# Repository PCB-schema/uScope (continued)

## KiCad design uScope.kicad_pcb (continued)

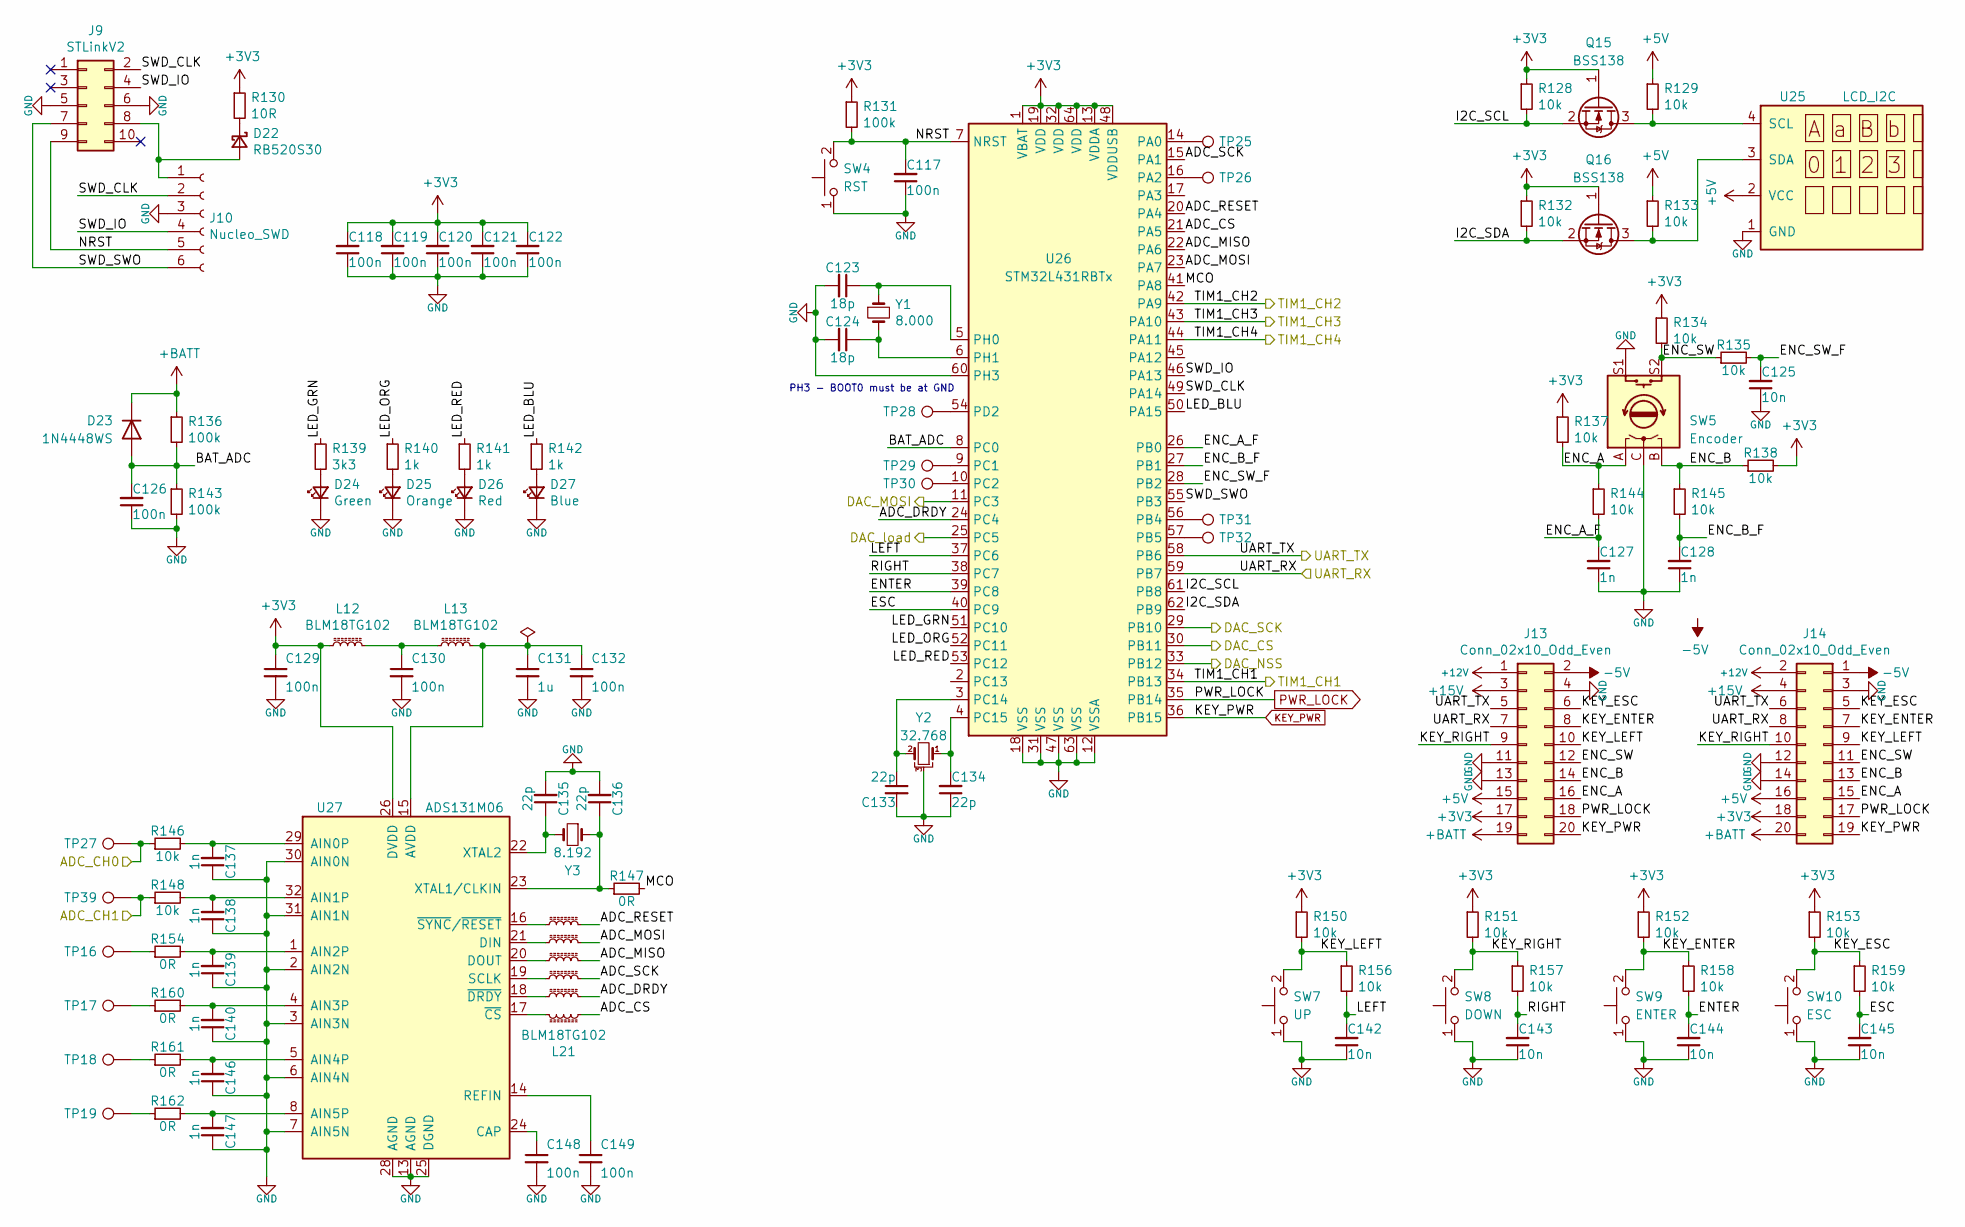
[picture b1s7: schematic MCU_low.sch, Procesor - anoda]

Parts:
C117, C118, C119, C120, C121, C122, C126, C129, C130, C132, C148, C149: 100n; C_0603_1608Metric
C123, C124: 18p; C_0603_1608Metric
C125, C142, C143, C144, C145: 10n; C_0603_1608Metric
C127, C128, C137, C138, C139, C140, C146, C147: 1n; C_0603_1608Metric
C131: 1u; C_0603_1608Metric
C133, C134, C135, C136: 22p; C_0603_1608Metric
D22: RB520S30; D_SOD-323-523_HandSoldering
D23: 1N4448WS; D_SOD-323-523_HandSoldering
D24: Green; D_0805_2012Metric_Pad1.15x1.40mm_HandSolder
D25: Orange; D_0805_2012Metric_Pad1.15x1.40mm_HandSolder
D26: Red; D_0805_2012Metric_Pad1.15x1.40mm_HandSolder
D27: Blue; D_0805_2012Metric_Pad1.15x1.40mm_HandSolder
J9: STLinkV2; ST-LinkV2_FakeStm8Stm32_vertical
J10: Nucleo_SWD; PinSocket_1x06_P2.54mm_Vertical
J13, J14: Conn_02x10_Odd_Even; PinSocket_2x10_P2.54mm_Vertical
L12, L13, L16, L17, L18, L19, L20, L21: BLM18TG102; L_0603_1608Metric
Q15, Q16: BSS138; SOT-23
R128, R129, R132, R133, R134, R135, R137, R138, R144, R145, R146, R148, R150, R151, R152, R153, R156, R157, R158, R159: 10k; R_0603_1608Metric
R130: 10R; R_0603_1608Metric
R131, R136, R143: 100k; R_0603_1608Metric
R139: 3k3; R_0603_1608Metric
R140, R141, R142: 1k; R_0603_1608Metric
R147, R154, R160, R161, R162: 0R; R_0603_1608Metric
SW4: RST; SW_Push_1P1T_NO_6x6mm_H9.5mm
SW5: Encoder; Encoder_12.4x13.4_pitch2.5mm_wSw
SW7: UP; SW_Push_1P1T_NO_6x6mm_H9.5mm
SW8: DOWN; SW_Push_1P1T_NO_6x6mm_H9.5mm
SW9: ENTER; SW_Push_1P1T_NO_6x6mm_H9.5mm
SW10: ESC; SW_Push_1P1T_NO_6x6mm_H9.5mm
TP16, TP17, TP18, TP19, TP25, TP26, TP27, TP28, TP29, TP30, TP31, TP32, TP39: TestPoint; TestPoint_THTPad_D1.5mm_Drill0.7mm
U25: LCD_I2C; PinHeader_1x04_P2.54mm_Vertical
U26: STM32L431RBTx; LQFP-64_10x10mm_P0.5mm
U27: ADS131M06; TQFP-32_5x5mm_P0.5mm_edges
Y1: 8.000; Crystal_HC49-4H_Vertical
Y2: 32.768; Crystal_C38-LF_D3.0mm_L8.0mm_Horizontal_1EP_style1
Y3: 8.192; Crystal_HC49-4H_Vertical

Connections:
+3V3: C118.2, C119.2, C120.2, C121.2, C122.2, C129.1, J13.17, J14.18, L12.1, Q15.1 (G), Q16.1 (G), R128.1, R130.1, R131.1, R132.1, R134.1, R137.1, R138.2, R150.1, R151.1, R152.1, R153.1, U26.1 (VBAT), U26.13 (VDDA), U26.19 (VDD), U26.32 (VDD), U26.48 (VDDUSB), U26.64 (VDD), U27.26 (DVDD); also elsewhere on the board
+5V: J13.15, J14.16, R129.1, R133.1, U25.2 (VCC); also elsewhere on the board
+12V: J13.1, J14.2; also elsewhere on the board
+15V: J13.3, J14.4; also elsewhere on the board
-5V: J13.2, J14.1; also elsewhere on the board
/ADC_IK: R146.1, TP27.1; also elsewhere on the board
/ADC_UK: R148.1, TP39.1; also elsewhere on the board
/LV_UART_RX: J13.7, J14.8, U26.59 (PB7); also elsewhere on the board
/LV_UART_TX: J13.5, J14.6, U26.58 (PB6); also elsewhere on the board
/MCU_low/ADC_CS: L21.1, U26.21 (PA5)
/MCU_low/ADC_DRDY: L20.2, U26.24 (PC4)
/MCU_low/ADC_MISO: L18.2, U26.22 (PA6)
/MCU_low/ADC_MOSI: L17.2, U26.23 (PA7)
/MCU_low/ADC_RESET: L16.2, U26.20 (PA4)
/MCU_low/ADC_SCK: L19.2, U26.15 (PA1)
/MCU_low/BAT_ADC: C126.2, D23.2 (A), R136.2, R143.1, U26.8 (PC0)
/MCU_low/DAC_CS: U26.30 (PB11); also elsewhere on the board
/MCU_low/DAC_MOSI: U26.11 (PC3); also elsewhere on the board
/MCU_low/DAC_NSS: U26.33 (PB12); also elsewhere on the board
/MCU_low/DAC_SCK: U26.29 (PB10); also elsewhere on the board
/MCU_low/DAC_load: U26.25 (PC5); also elsewhere on the board
/MCU_low/ENC_A: J13.16, J14.15, R137.2, R144.1, SW5.A
/MCU_low/ENC_A_F: C127.2, R144.2, U26.26 (PB0)
/MCU_low/ENC_B: J13.14, J14.13, R138.1, R145.1, SW5.B
/MCU_low/ENC_B_F: C128.2, R145.2, U26.27 (PB1)
/MCU_low/ENC_SW: J13.12, J14.11, R134.2, R135.1, SW5.S2
/MCU_low/ENC_SW_F: C125.2, R135.2, U26.28 (PB2)
/MCU_low/ENTER: C144.2, R158.2, U26.39 (PC8)
/MCU_low/ESC: C145.2, R159.2, U26.40 (PC9)
/MCU_low/I2C_SCL: Q15.2 (S), R128.2, U26.61 (PB8)
/MCU_low/I2C_SDA: Q16.2 (S), R132.2, U26.62 (PB9)
/MCU_low/KEY_ENTER: J13.8, J14.7, R152.2, R158.1, SW9.2
/MCU_low/KEY_ESC: J13.6, J14.5, R153.2, R159.1, SW10.2
/MCU_low/KEY_LEFT: J13.10, J14.9, R150.2, R156.1, SW7.2
/MCU_low/KEY_RIGHT: J13.9, J14.10, R151.2, R157.1, SW8.2
/MCU_low/LED_BLU: R142.1, U26.50 (PA15)
/MCU_low/LED_GRN: R139.1, U26.51 (PC10)
/MCU_low/LED_ORG: R140.1, U26.52 (PC11)
/MCU_low/LED_RED: R141.1, U26.53 (PC12)
/MCU_low/LEFT: C142.2, R156.2, U26.37 (PC6)
/MCU_low/MCO: R147.2, U26.41 (PA8)
/MCU_low/NRST: C117.2, J9.9, J10.5, R131.2, SW4.2, U26.7 (NRST)
/MCU_low/RIGHT: C143.2, R157.2, U26.38 (PC7)
/MCU_low/SWD_CLK: J9.2, J10.2, U26.49 (PA14)
/MCU_low/SWD_IO: J9.4, J10.4, U26.46 (PA13)
/MCU_low/SWD_SWO: J9.7, J10.6, U26.55 (PB3)
/MCU_low/TIM1_CH1: U26.34 (PB13); also elsewhere on the board
/MCU_low/TIM1_CH2: U26.42 (PA9); also elsewhere on the board
/MCU_low/TIM1_CH3: U26.43 (PA10); also elsewhere on the board
/MCU_low/TIM1_CH4: U26.44 (PA11); also elsewhere on the board
KEY_PWR: J13.20, J14.19, U26.36 (PB15); also elsewhere on the board
unnamed: C123.1, U26.5 (PH0), Y1.1
unnamed: C124.1, U26.6 (PH1), Y1.2
unnamed: C130.1, L12.2, L13.1
unnamed: C131.1, C132.1, L13.2, U27.15 (AVDD)
unnamed: C133.1, U26.3 (PC14), Y2.2
unnamed: C134.2, U26.4 (PC15), Y2.1
unnamed: C135.1, U27.22 (XTAL2), Y3.2
unnamed: C136.1, R147.1, U27.23 (XTAL1/CLKIN), Y3.1
unnamed: C137.2, R146.2, U27.29 (AIN0P)
unnamed: C138.2, R148.2, U27.32 (AIN1P)
unnamed: C139.2, R154.2, U27.1 (AIN2P)
unnamed: C140.2, R160.2, U27.4 (AIN3P)
unnamed: C146.2, R161.2, U27.5 (AIN4P)
unnamed: C147.2, R162.2, U27.8 (AIN5P)
unnamed: C148.1, U27.24 (CAP)
unnamed: C149.1, U27.14 (REFIN)
unnamed: D22.1 (K), R130.2
unnamed: D22.2 (A), J9.8, J10.1
unnamed: D24.2 (A), R139.2
unnamed: D25.2 (A), R140.2
unnamed: D26.2 (A), R141.2
unnamed: D27.2 (A), R142.2
unnamed: L16.1, U27.16 (~SYNC~/~RESET)
unnamed: L17.1, U27.21 (DIN)
unnamed: L18.1, U27.20 (DOUT)
unnamed: L19.1, U27.19 (SCLK)
unnamed: L20.1, U27.18 (~DRDY)
unnamed: L21.2, U27.17 (~CS)
unnamed: Q15.3 (D), R129.2, U25.4 (SCL)
unnamed: Q16.3 (D), R133.2, U25.3 (SDA)
unnamed: R154.1, TP16.1
unnamed: R160.1, TP17.1
unnamed: R161.1, TP18.1
unnamed: R162.1, TP19.1
unnamed: TP25.1, U26.14 (PA0)
unnamed: TP26.1, U26.16 (PA2)
unnamed: TP28.1, U26.54 (PD2)
unnamed: TP29.1, U26.9 (PC1)
unnamed: TP30.1, U26.10 (PC2)
unnamed: TP31.1, U26.56 (PB4)
unnamed: TP32.1, U26.57 (PB5)
PWR_LOCK: J13.18, J14.17, U26.35 (PB14); also elsewhere on the board

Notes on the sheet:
PH3 - BOOT0 must be at GND

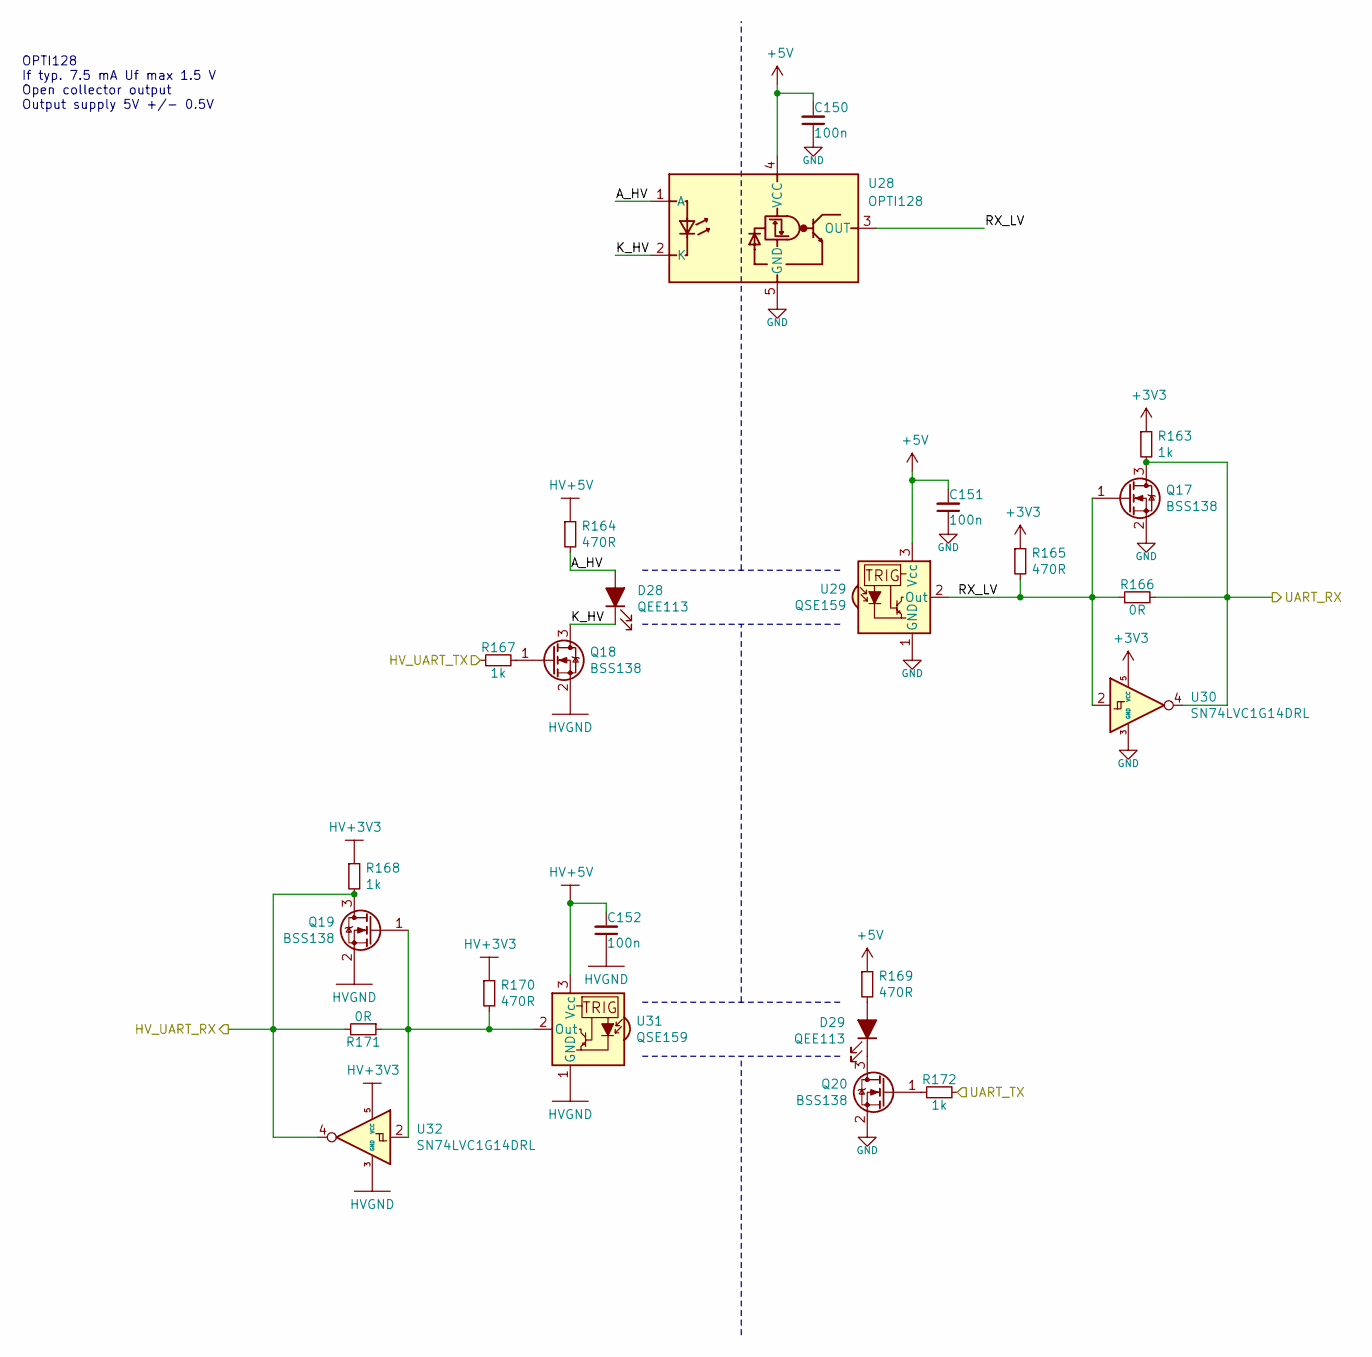
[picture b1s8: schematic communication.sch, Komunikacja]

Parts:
C150, C151, C152: 100n; C_0603_1608Metric
D28, D29: QEE113; ONsemi_QEE113
Q17, Q18, Q19, Q20: BSS138; SOT-23
R163, R167, R168, R172: 1k; R_0603_1608Metric
R164, R165, R169, R170: 470R; R_0603_1608Metric
R166, R171: 0R; R_0603_1608Metric
U28: OPTI128; OPTI12x
U29, U31: QSE159; ONSemi_QSE15x
U30, U32: SN74LVC1G14DRL; SOT-553

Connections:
+3V3: R163.1, R165.1, U30.5 (VCC); also elsewhere on the board
+5V: C150.2, C151.2, R169.1, U28.4 (VCC), U29.3 (Vcc); also elsewhere on the board
/HV_UART_RX: Q19.3 (D), R168.2, R171.2, U32.4; also elsewhere on the board
/HV_UART_TX: R167.1; also elsewhere on the board
/LV_UART_RX: Q17.3 (D), R163.2, R166.2, U30.4; also elsewhere on the board
/LV_UART_TX: R172.2; also elsewhere on the board
/communication/A_HV: D28.2 (A), R164.2, U28.1 (A)
/communication/K_HV: D28.1 (K), Q18.3 (D), U28.2 (K)
/communication/RX_LV: Q17.1 (G), R165.2, R166.1, U28.3 (OUT), U29.2 (Out), U30.2
HV+3V3: R168.1, R170.1, U32.5 (VCC); also elsewhere on the board
HV+5V: C152.2, R164.1, U31.3 (Vcc); also elsewhere on the board
unnamed: D29.1 (K), Q20.3 (D)
unnamed: D29.2 (A), R169.2
unnamed: Q18.1 (G), R167.2
unnamed: Q19.1 (G), R170.2, R171.1, U31.2 (Out), U32.2
unnamed: Q20.1 (G), R172.1

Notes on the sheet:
OPTI128 If typ. 7.5 mA Uf max 1.5 V Open collector output Output supply 5V +/- 0.5V

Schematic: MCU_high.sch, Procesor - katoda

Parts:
C153, C154, C156, C160, C161, C162, C163, C164, C169, C171, C172: 100n; C_0603_1608Metric
C155: 1u; C_0603_1608Metric
C157, C158, C175, C176: 22p; C_0603_1608Metric
C159, C165, C166, C167, C168, C170: 1n; C_0603_1608Metric
C173, C174: 18p; C_0603_1608Metric
D30: RB520S30; D_SOD-323-523_HandSoldering
D31: Green; D_0805_2012Metric_Pad1.15x1.40mm_HandSolder
D32: Orange; D_0805_2012Metric_Pad1.15x1.40mm_HandSolder
D33: Red; D_0805_2012Metric_Pad1.15x1.40mm_HandSolder
D34: Blue; D_0805_2012Metric_Pad1.15x1.40mm_HandSolder
J11: STLinkV2; ST-LinkV2_FakeStm8Stm32_vertical
J12: Nucleo_SWD; PinSocket_1x06_P2.54mm_Vertical
J15, J16: Conn_02x03_Odd_Even; PinSocket_2x03_P2.54mm_Vertical
L14, L15, L22, L23, L24, L25, L26, L27: BLM18TG102; L_0603_1608Metric
R173: 10R; R_0603_1608Metric
R174, R176: 10k; R_0603_1608Metric
R175, R177, R178, R181, R182: 0R; R_0603_1608Metric
R180: 100k; R_0603_1608Metric
R183: 3k3; R_0603_1608Metric
R184, R185, R186: 1k; R_0603_1608Metric
SW11: RST; SW_Push_1P1T_NO_6x6mm_H9.5mm
TP5, TP6, TP7, TP8, TP9, TP10, TP11, TP12, TP20, TP21, TP22, TP23, TP33, TP34, TP35, TP36, TP37, TP38, TP40, TP41, TP42, TP43, TP44, TP45, TP46: TestPoint; TestPoint_THTPad_D1.5mm_Drill0.7mm
U33: ADS131M06; TQFP-32_5x5mm_P0.5mm_edges
U34: STM32L431RBTx; LQFP-64_10x10mm_P0.5mm
Y4: 8.192; Crystal_HC49-4H_Vertical
Y5: 8.000; Crystal_HC49-4H_Vertical
Y6: 32.768; Crystal_C38-LF_D3.0mm_L8.0mm_Horizontal_1EP_style1

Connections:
/ADC_UE: J15.4, J16.3, R174.1, TP40.1; also elsewhere on the board
/ADC_UF: J15.6, J16.5, R176.1, TP11.1, TP12.1, TP41.1; also elsewhere on the board
/HV_UART_RX: U34.59 (PB7); also elsewhere on the board
/HV_UART_TX: U34.58 (PB6); also elsewhere on the board
/MCU_high/ADC_CS: L27.1, U34.21 (PA5)
/MCU_high/ADC_DRDY: L26.2, U34.24 (PC4)
/MCU_high/ADC_MISO: L24.2, U34.22 (PA6)
/MCU_high/ADC_MOSI: L23.2, U34.23 (PA7)
/MCU_high/ADC_RESET: L22.2, U34.20 (PA4)
/MCU_high/ADC_SCK: L25.2, U34.15 (PA1)
/MCU_high/LED_BLU: R186.1, U34.50 (PA15)
/MCU_high/LED_GRN: R183.1, U34.51 (PC10)
/MCU_high/LED_ORG: R184.1, U34.52 (PC11)
/MCU_high/LED_RED: R185.1, U34.53 (PC12)
/MCU_high/MCO: R175.2, U34.41 (PA8)
/MCU_high/NRST: C169.2, J11.9, J12.5, R180.2, SW11.2, U34.7 (NRST)
/MCU_high/SWD_CLK: J11.2, J12.2, U34.49 (PA14)
/MCU_high/SWD_IO: J11.4, J12.4, U34.46 (PA13)
/MCU_high/SWD_SWO: J11.7, J12.6, U34.55 (PB3)
HV+3V3: C153.1, C160.2, C161.2, C162.2, C163.2, C164.2, L14.1, R173.1, R180.1, U33.26 (DVDD), U34.1 (VBAT), U34.13 (VDDA), U34.19 (VDD), U34.32 (VDD), U34.48 (VDDUSB), U34.64 (VDD); also elsewhere on the board
HV+5V: J15.3, J16.4, TP5.1, TP6.1; also elsewhere on the board
HV-5V: J15.5, J16.6, TP7.1, TP8.1; also elsewhere on the board
unnamed: C154.1, L14.2, L15.1
unnamed: C155.1, C156.1, L15.2, U33.15 (AVDD)
unnamed: C157.1, U33.22 (XTAL2), Y4.2
unnamed: C158.1, R175.1, U33.23 (XTAL1/CLKIN), Y4.1
unnamed: C159.2, R174.2, U33.29 (AIN0P)
unnamed: C165.2, R176.2, U33.32 (AIN1P)
unnamed: C166.2, R177.2, U33.1 (AIN2P)
unnamed: C167.2, R178.2, U33.4 (AIN3P)
unnamed: C168.2, R181.2, U33.5 (AIN4P)
unnamed: C170.2, R182.2, U33.8 (AIN5P)
unnamed: C171.1, U33.24 (CAP)
unnamed: C172.1, U33.14 (REFIN)
unnamed: C173.1, U34.5 (PH0), Y5.1
unnamed: C174.1, U34.6 (PH1), Y5.2
unnamed: C175.1, U34.3 (PC14), Y6.1
unnamed: C176.2, U34.4 (PC15), Y6.2
unnamed: D30.1 (K), R173.2
unnamed: D30.2 (A), J11.8, J12.1
unnamed: D31.2 (A), R183.2
unnamed: D32.2 (A), R184.2
unnamed: D33.2 (A), R185.2
unnamed: D34.2 (A), R186.2
unnamed: L22.1, U33.16 (~SYNC~/~RESET)
unnamed: L23.1, U33.21 (DIN)
unnamed: L24.1, U33.20 (DOUT)
unnamed: L25.1, U33.19 (SCLK)
unnamed: L26.1, U33.18 (~DRDY)
unnamed: L27.2, U33.17 (~CS)
unnamed: R177.1, TP20.1
unnamed: R178.1, TP21.1
unnamed: R181.1, TP22.1
unnamed: R182.1, TP23.1
unnamed: TP33.1, U34.16 (PA2)
unnamed: TP34.1, U34.17 (PA3)
unnamed: TP35.1, U34.42 (PA9)
unnamed: TP36.1, U34.43 (PA10)
unnamed: TP37.1, U34.44 (PA11)
unnamed: TP38.1, U34.45 (PA12)
unnamed: TP43.1, U34.33 (PB12)
unnamed: TP44.1, U34.34 (PB13)
unnamed: TP45.1, U34.35 (PB14)
unnamed: TP46.1, U34.36 (PB15)

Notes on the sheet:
PH3 - BOOT0 must be at GND

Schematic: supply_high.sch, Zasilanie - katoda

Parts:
C83, C184, C192, C198: 10u; C_0603_1608Metric_Pad1.05x0.95mm_HandSolder
C177, C179, C182, C188, C191, C194, C195, C197: 100n; C_0603_1608Metric
C178, C180, C196: 2u2; C_0805_2012Metric
C181, C185, C187, C189: 1u; C_0603_1608Metric
C183: 10n; C_0603_1608Metric
C190: nc; C_0603_1608Metric
D13, D35, D36, D37, D38: 1N4448; D_SOD-323-523_HandSoldering
Q21: BC817; SOT-23
R187, R194: 560R; R_0603_1608Metric_Pad1.05x0.95mm_HandSolder
R188, R188b, R192: 3k3; R_0603_1608Metric_Pad1.05x0.95mm_HandSolder
R189: 4k7; R_0603_1608Metric
R190: 0R; R_0603_1608Metric
R191: nc; R_0603_1608Metric
R192b: 3k3
R193: 68k; R_0603_1608Metric_Pad1.05x0.95mm_HandSolder
R195: 10k; R_0603_1608Metric_Pad1.05x0.95mm_HandSolder
U35: LM317L_SOT89; SOT-89-3
U36: LP2985-3.3; SOT-23-5
U37: TL432; SOT-23
U38: TC7660S; SOIC-8_3.9x4.9mm_P1.27mm
U39: LM337L_SO8; SOIC-8_3.9x4.9mm_P1.27mm

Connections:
HV+3V3: C184.1, C185.1, D13.2 (A), U36.5 (VOUT); also elsewhere on the board
HV+5V: C179.1, C180.1, C181.1, C182.1, D13.1 (K), D35.2 (A), D36.1 (K), R187.1, U35.2 (VO), U36.1 (VIN), U36.3 (ON/~OFF~); also elsewhere on the board
HV+12V: C177.1, C178.1, D35.1 (K), Q21.3 (C), R189.1, R190.1, U35.3 (VI); also elsewhere on the board
HV-5V: C195.1, C196.1, D37.2 (A), D38.1 (K), R194.2, U39.1 (VO); also elsewhere on the board
unnamed: C183.1, U36.4 (BP)
unnamed: C187.1, D36.2 (A), R187.2, R188.1, R188b.1, U35.1 (ADJ)
unnamed: C83.1, C188.2, Q21.2 (E), R190.2, R191.1, U38.8 (V+)
unnamed: C189.2, D37.1 (K), R192.2, R192b.2, R194.1, U39.4 (ADJ)
unnamed: C190.1, U38.7 (OSC)
unnamed: C191.1, C192.2, C194.1, D38.2 (A), U38.5 (VOUT), U39.2 (VI), U39.3 (VI), U39.6 (VI), U39.7 (VI)
unnamed: C197.1, C198.1, U38.2 (CAP+)
unnamed: C197.2, C198.2, U38.4 (CAP-)
unnamed: Q21.1 (B), R189.2, R193.1, U37.2 (K)
unnamed: R191.2, U38.1 (BOOST)
unnamed: R193.2, R195.1, U37.1 (REF)

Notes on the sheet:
+12V to -12V
-12V to -5V
+12V to +5V
+5V to +3V3

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
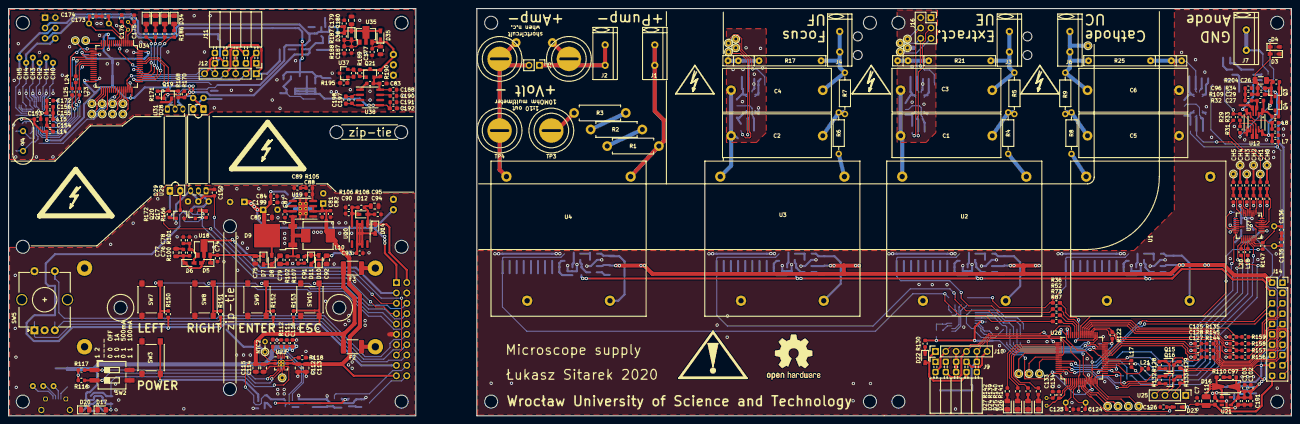
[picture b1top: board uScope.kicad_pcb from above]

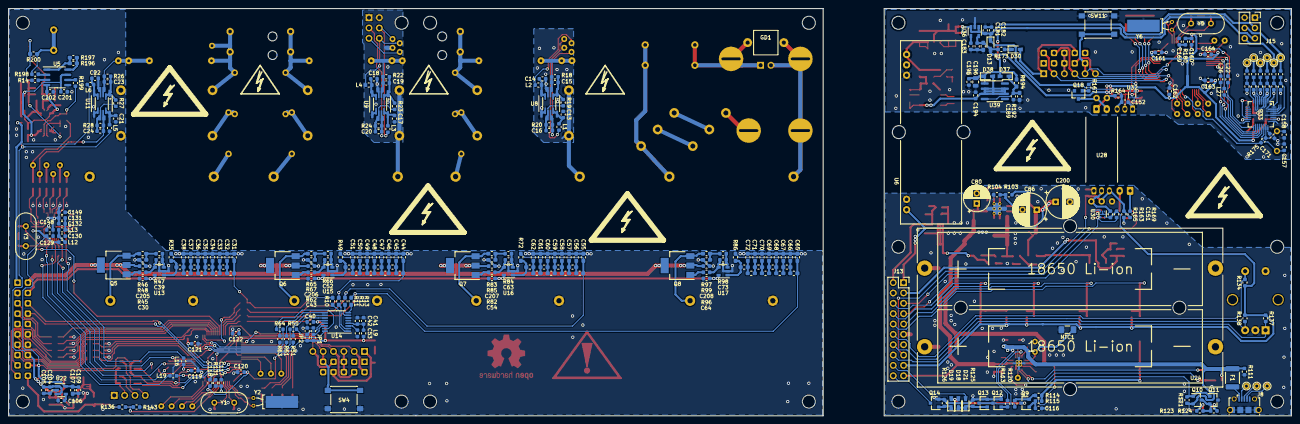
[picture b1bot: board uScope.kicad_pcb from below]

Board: 2 copper layers, 315.0 x 100.0 mm, 591 parts (293 on the bottom side), 336 nets.

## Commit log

2020-08-22 - More schematics, - gitignore
2020-08-22 - schematic as hierarchical - added cache lib
2020-08-22 - moved voltmeters to separate sheet - hierarchical sheets
2020-09-15 - added DC/DC converter to library, - moved ammeter & drivers to sub-sheet, - further develop
2020-09-16 - added supply sch draft
2020-09-21 - battery charger develop - added sheet (every sheet contains total number of sheets, thats beacouse here are changes in all sheets)
2020-09-21 - supply converter develop - added sheet: MCU - cleanup 'koncepcja' sub-schematics
2020-09-21 - added sheet: MCU
2020-09-23 - added footprint & 3D model of DC/DC HV converter - updated battery (to 2x battery holder) - some changes in supply
2020-10-09 - changes..
2020-10-13 - W.i.P.
2020-10-14 - MCU_Low: added encoder, DAC, alternate MCU
2020-10-22 - drivers modified - MCU replaced
2020-10-23 - connect things to MCUlow (DAC, screen, keys, debug) - improvement in charger (read PWR key)
2020-11-02 - high side (supply, MCU) - low side MCU - much small changes
2020-11-02 - final schematic
2020-11-03 - init PCB - fix last things in schematic
2020-11-03 - first segregation on pcb
2020-11-05 - pcb placement, add 3dShapes
2020-11-09 - PCB progress
2020-11-11 - PCB WiP - Pump output aligned
2020-11-13 - PCB WiP
2020-11-19 - PCB WiP - polygons on PCB small
2020-11-25 - PCB final !!!!! before DRC
2020-11-25 - PCB final before split
2021-03-14 - as-built changes - add custom library elements
2021-03-14 - add 3D views
2021-03-14 - update schematic pdf print
